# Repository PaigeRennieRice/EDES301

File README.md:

# EDES301
Respository for EDES301 course work

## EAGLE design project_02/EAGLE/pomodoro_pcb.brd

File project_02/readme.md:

This file contains the full PCB design for my Pomodoro Study Timer built around the PocketBeagle.
Included are my Eagle schematic, board layout, custom library, mechanical drawing, Gerbers, and BOM.
To create the board board, I used a seven-segnment display (HT16K33), two pushbuttons, a potentiometer, a buzzer, and seven LEDs.
Gerbers in the docs/ folder were used to generate MacroFab quotes for 1/10/100/1000 units.
See docs/ for the schematic PDF, mechanical layout, and top/bottom copper previews.
Designed by Paige Rennie for EDES 301 (Fall 2025).

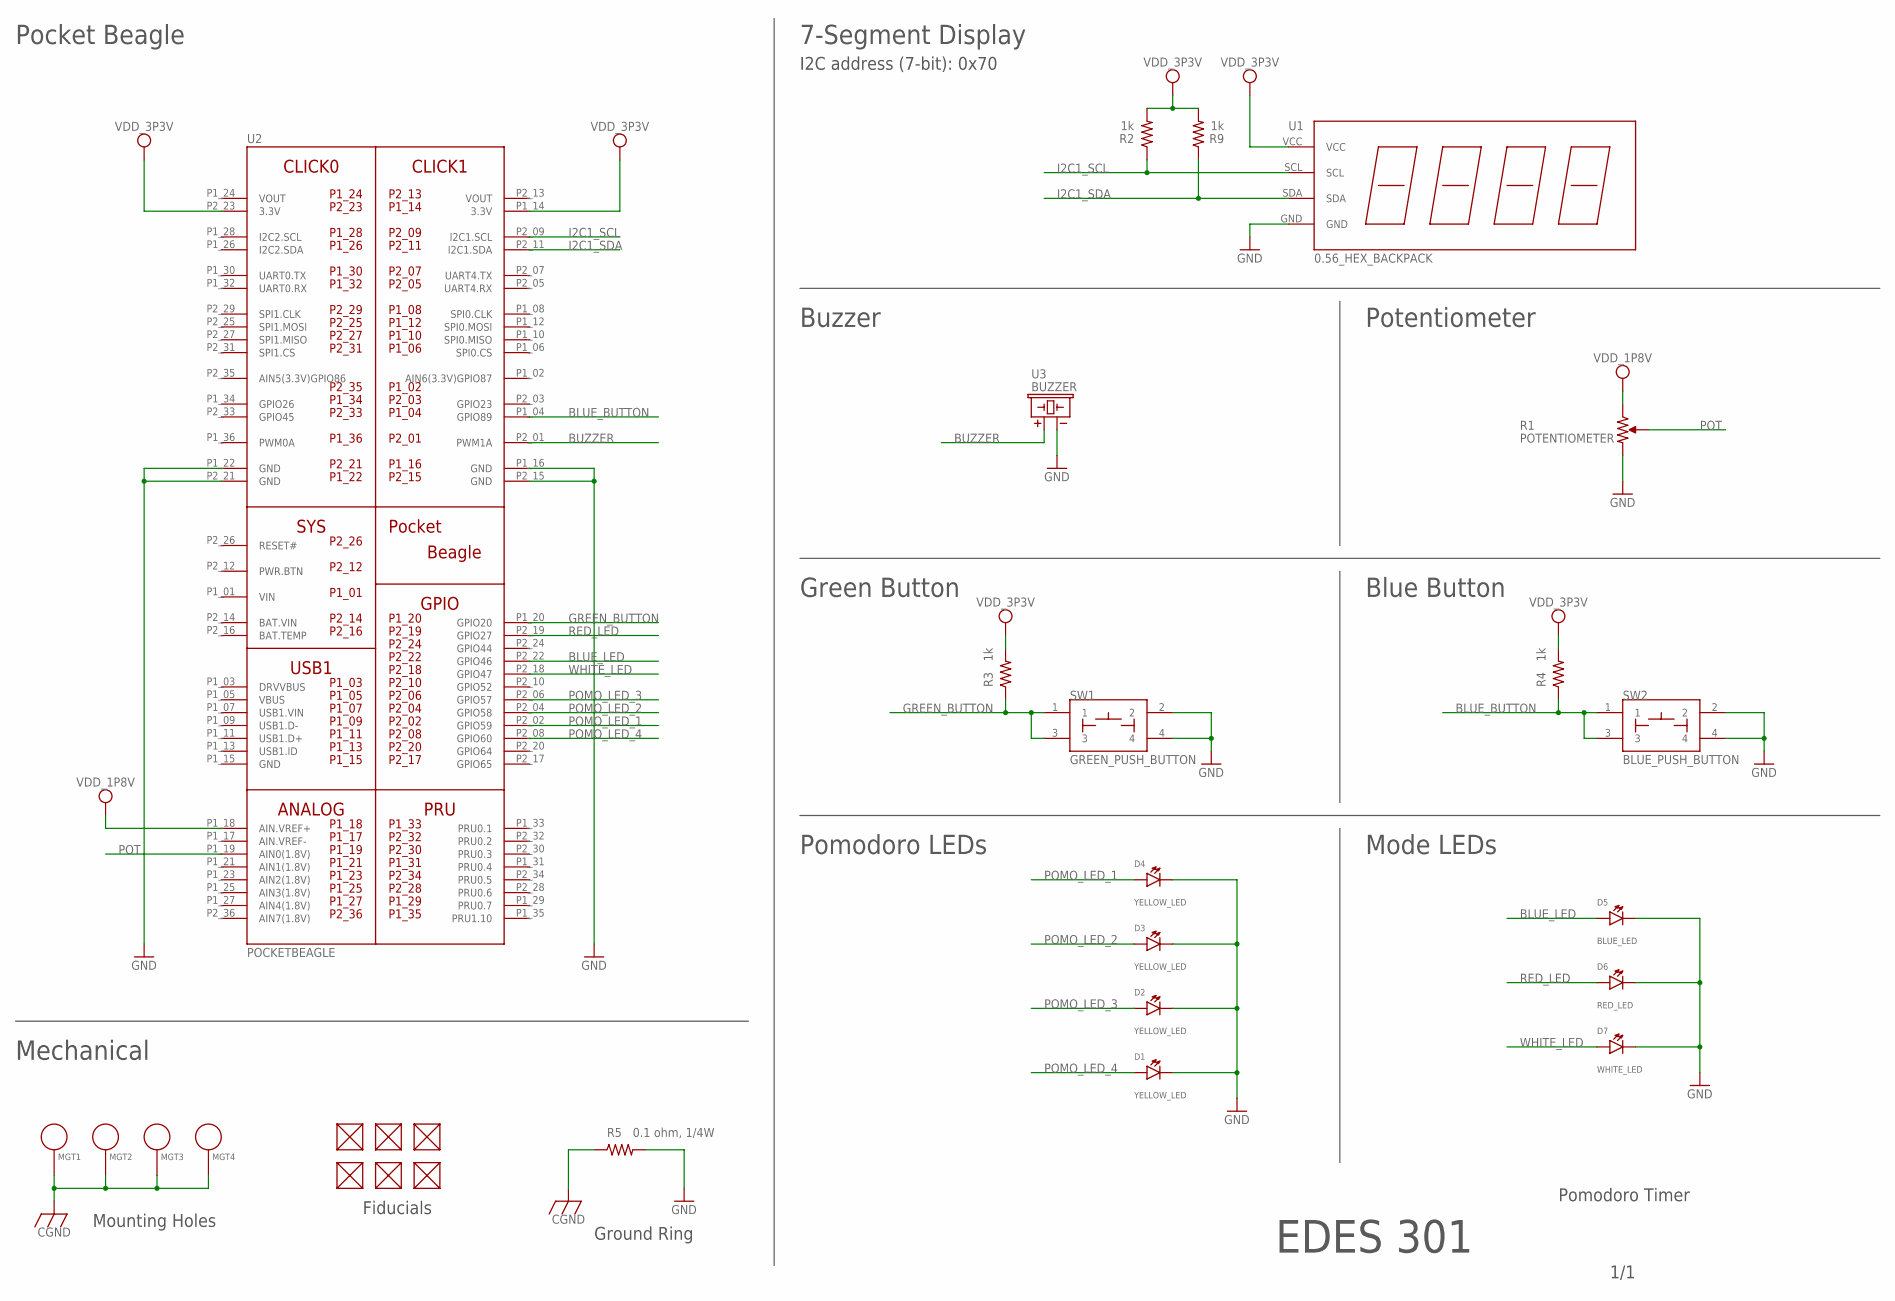
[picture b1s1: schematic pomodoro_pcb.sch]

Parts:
D1, D2, D3, D4: YELLOW_LED; EIA-STD
D5: BLUE_LED; EIA-STD
D6: RED_LED; EIA-STD
D7: WHITE_LED; EIA-STD
FUD1, FUD2, FUD3, FUD4, FUD5, FUD6: FIDUCIAL; FIDUCIAL_40MIL
MGT1, MGT2, MGT3, MGT4: MOUNTING_HOLE
R1: POTENTIOMETER; POT-PO90S
R2, R3, R4, R9: 1k; R0603
R5: 0.1 ohm, 1/4W; R0603
SW1: GREEN_PUSH_BUTTON; BUTTON_12.5MM
SW2: BLUE_PUSH_BUTTON; BUTTON_12.5MM
U1: 0.56_HEX_BACKPACK
U2: POCKETBEAGLE
U3: BUZZER; BUZZER_6.5MM

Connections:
BAT.VIN: U2.P2_14 (BAT.VIN)
BLUE_BUTTON: R4.1, SW2.1, SW2.3, U2.P1_04 (GPIO89)
BLUE_LED: D5.ANODE, U2.P2_22 (GPIO46)
BUZZER: U2.P2_01 (PWM1A), U3.+
CGND: MGT1.P$1, MGT2.P$1, MGT3.P$1, MGT4.P$1, R5.1
GND: D1.CATHODE, D2.CATHODE, D3.CATHODE, D4.CATHODE, D5.CATHODE, D6.CATHODE, D7.CATHODE, R1.CW, R5.2, SW1.2, SW1.4, SW2.2, SW2.4, U1.GND, U2.P1_16 (GND), U2.P1_22 (GND), U2.P2_15 (GND), U2.P2_21 (GND), U3.-
GREEN_BUTTON: R3.1, SW1.1, SW1.3, U2.P1_20 (GPIO20)
I2C1_SCL: R2.1, U1.SCL, U2.P2_09 (I2C1.SCL)
I2C1_SDA: R9.1, U1.SDA, U2.P2_11 (I2C1.SDA)
POMO_LED_1: D4.ANODE, U2.P2_02 (GPIO59)
POMO_LED_2: D3.ANODE, U2.P2_04 (GPIO58)
POMO_LED_3: D2.ANODE, U2.P2_06 (GPIO57)
POMO_LED_4: D1.ANODE, U2.P2_08 (GPIO60)
POT: R1.S, U2.P1_19 (AIN0(1.8V))
RED_LED: D6.ANODE, U2.P2_19 (GPIO27)
VDD_1P8V: R1.CCW, U2.P1_18 (AIN.VREF+)
VDD_3P3V: R2.2, R3.2, R4.2, R9.2, U1.VCC, U2.P1_14 (3.3V), U2.P2_23 (3.3V)
VIN: U2.P1_01 (VIN)
VOUT: U2.P1_24 (VOUT), U2.P2_13 (VOUT)
WHITE_LED: D7.ANODE, U2.P2_18 (GPIO47)

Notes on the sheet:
7-Segment Display
Buzzer
Green Button
Pocket Beagle
Potentiometer
Blue Button
Pomodoro LEDs
Mode LEDs
I2C address (7-bit): 0x70
Pomodoro Timer
EDES 301
1/1
Mechanical
Fiducials
Ground Ring
Mounting Holes

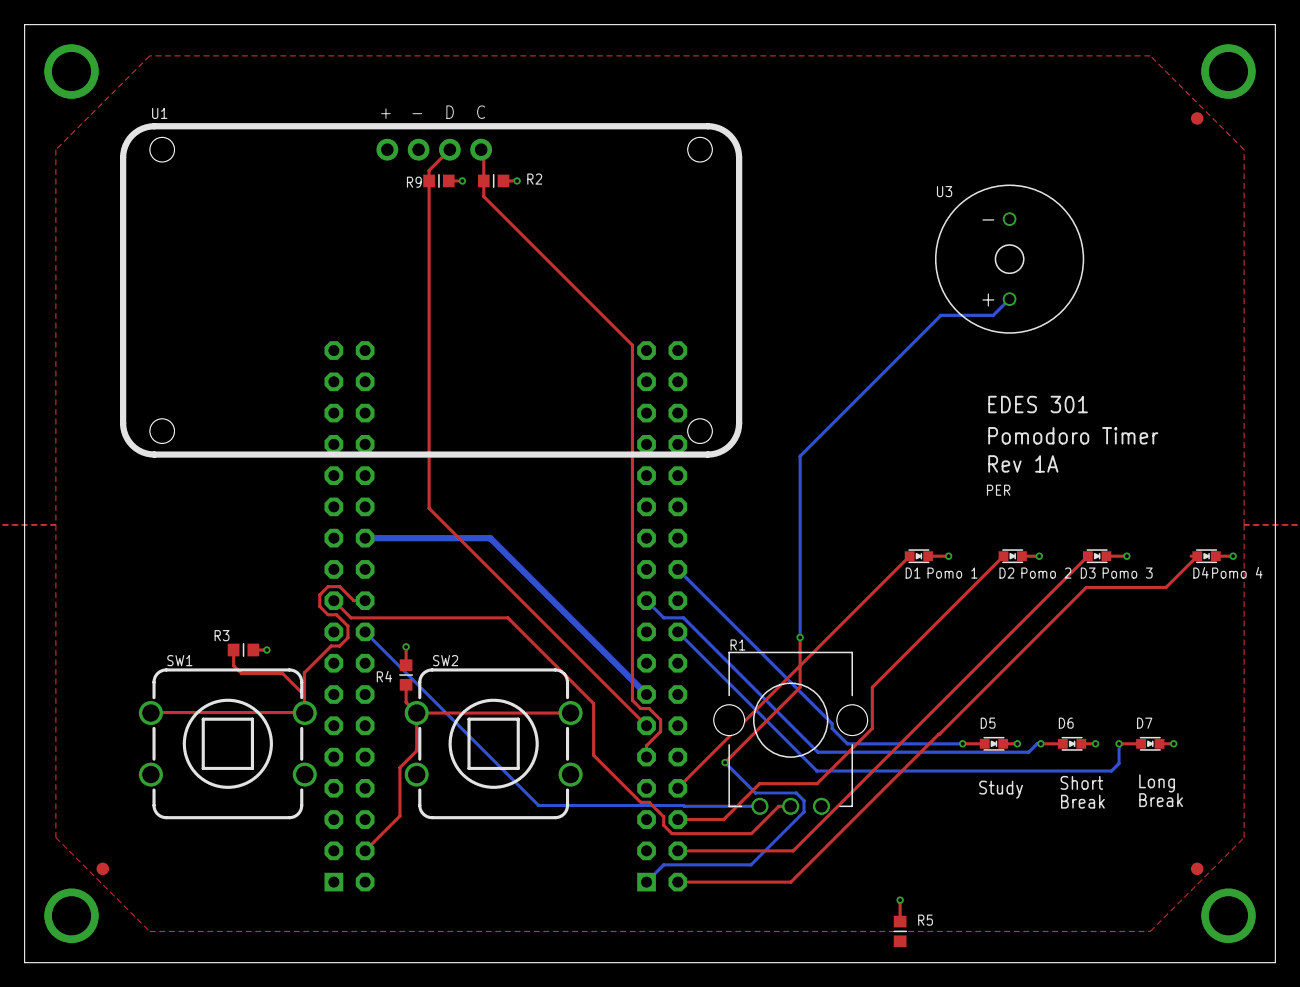
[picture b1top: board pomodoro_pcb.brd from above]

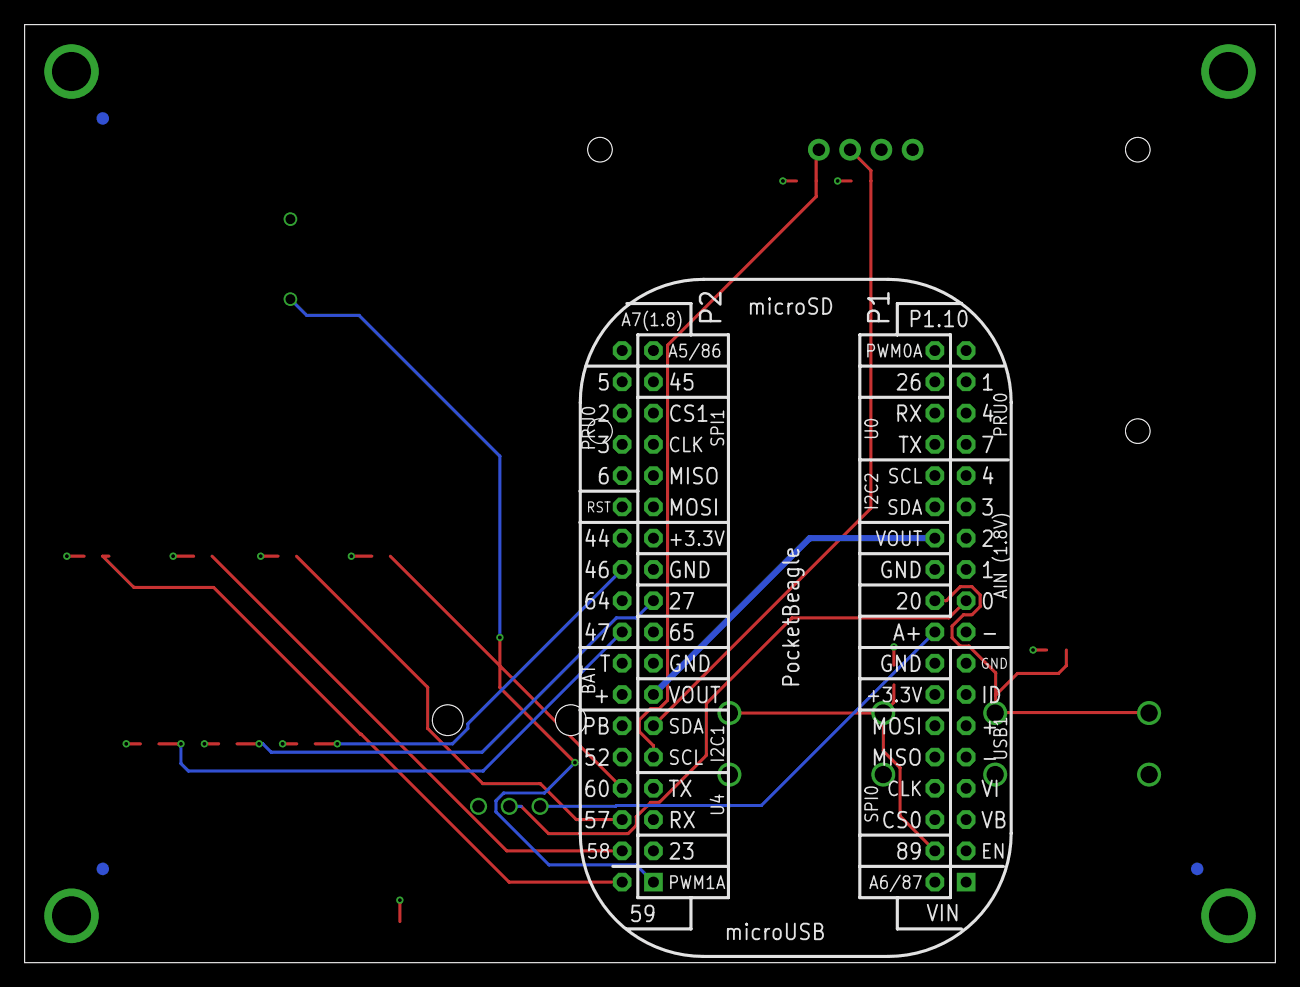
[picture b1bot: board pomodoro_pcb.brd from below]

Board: 4 copper layers, 101.6 x 76.2 mm, 28 parts (4 on the bottom side), 18 nets.

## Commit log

2025-09-19 Updating README.md
2025-09-30 Hello_World
2025-09-30 temp.txt
2025-10-06 Create project_01
2025-10-06 Create 1
2025-10-07 feat: Completed simple calculator logic with error handling
2025-10-07 feat: Completed simple calculator logic addition
2025-10-07 feat: Completed simple calculator logic addition and python 2 capability
2025-10-07 Updating code
2025-10-07 Edited code for button
2025-10-22 adding file
2025-10-22 updating files
2025-10-23 adding potentiometer
2025-10-28 combo_lock
2025-10-29 updating combo_lock
2025-11-03 new files, buzzer, servo
2025-11-03 adding threaded_button
2025-12-01 uploading project 1 code
2025-12-01 fixing bug
2025-12-15 Create EAGLE
2025-12-16 Create kkk
2025-12-16 Create ggg
